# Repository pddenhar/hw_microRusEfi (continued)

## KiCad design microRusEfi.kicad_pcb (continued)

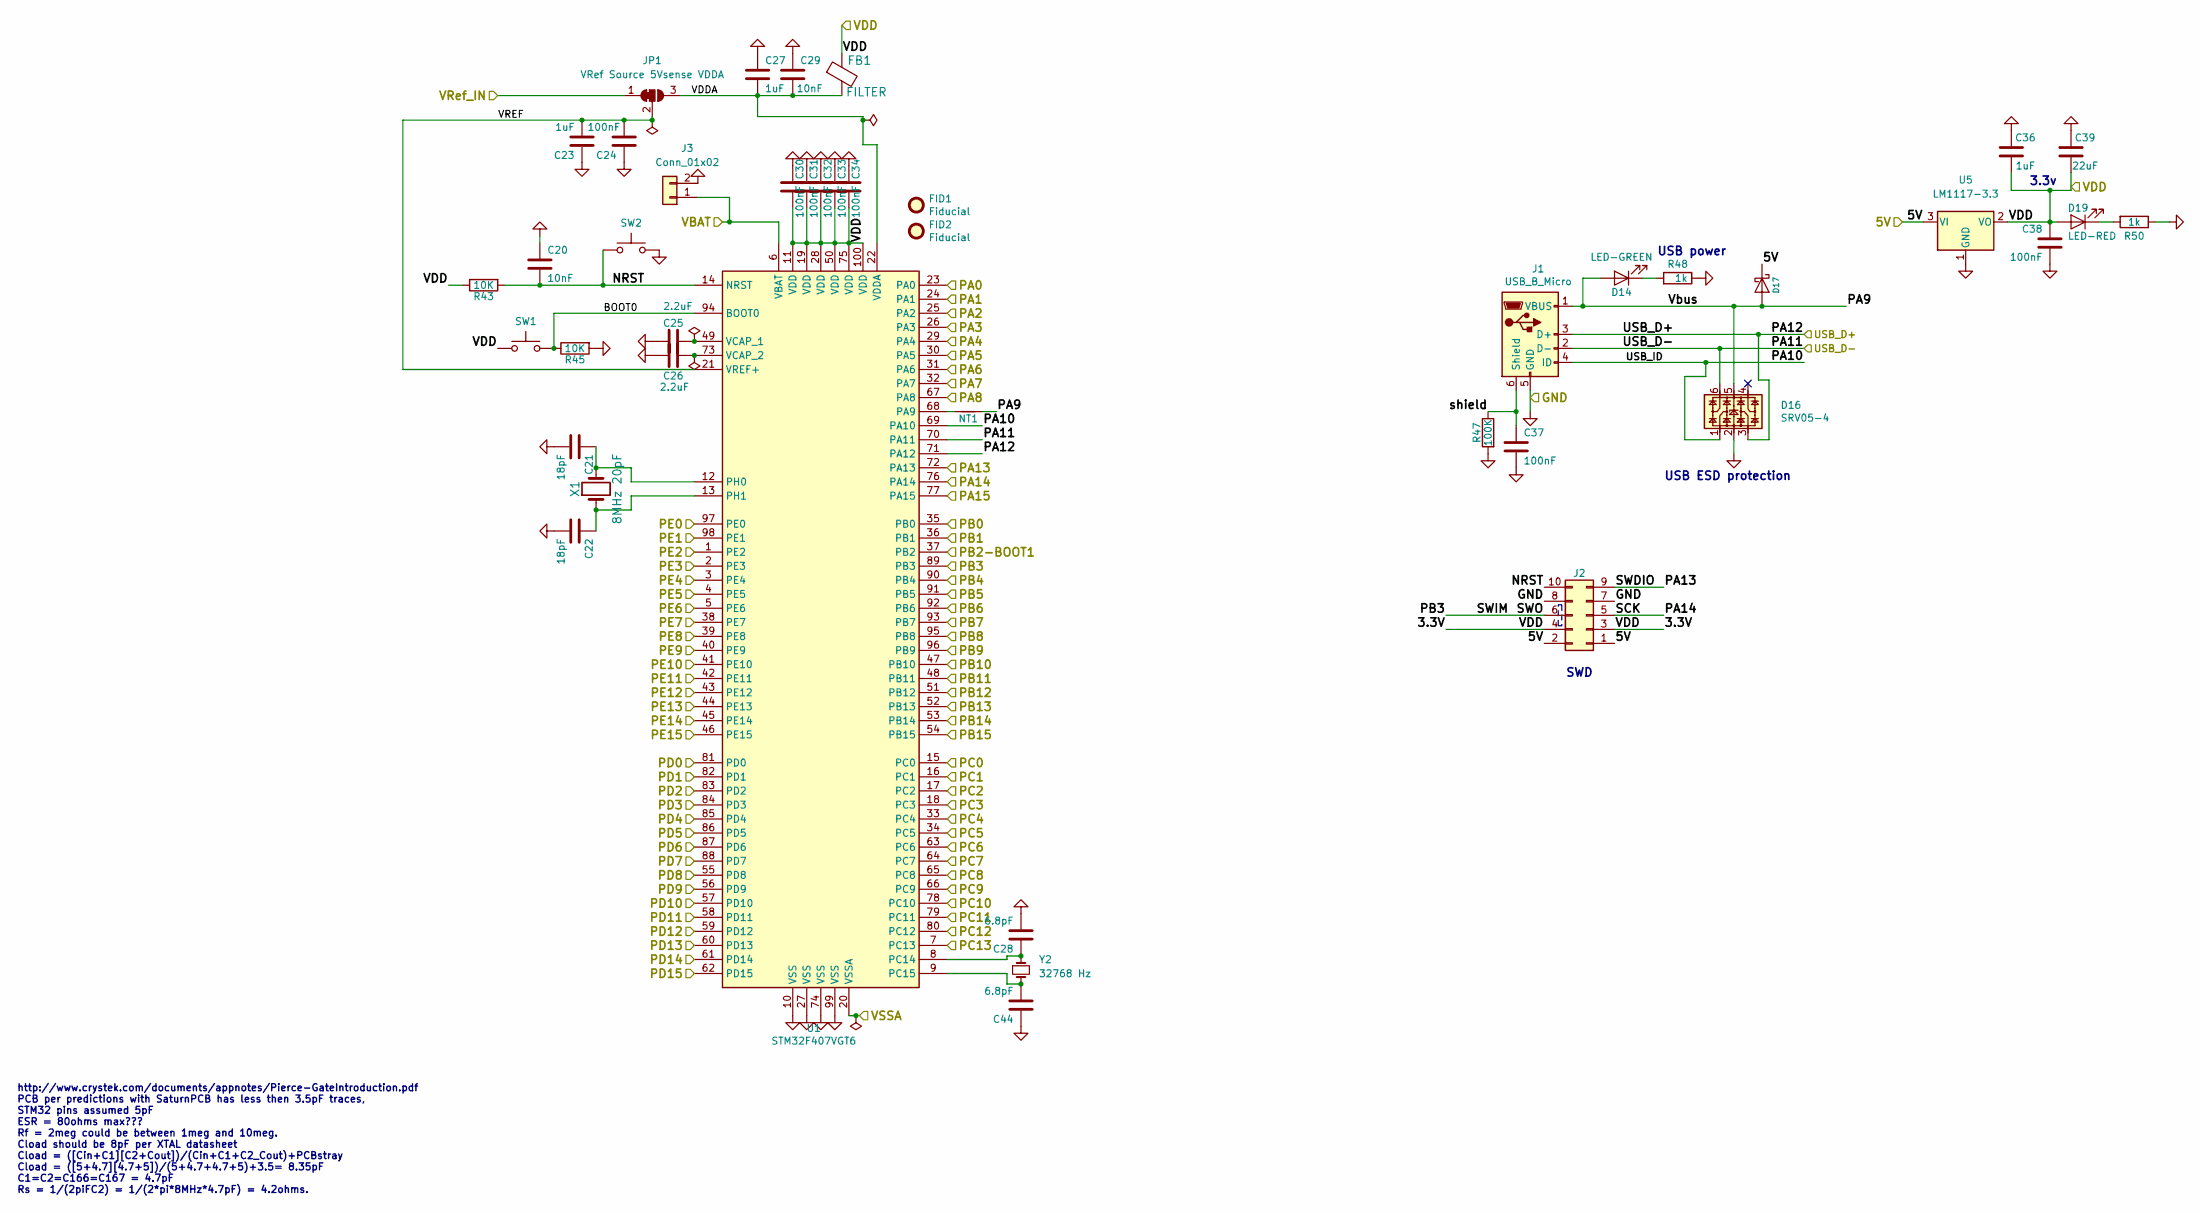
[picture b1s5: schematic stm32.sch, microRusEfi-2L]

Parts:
C20, C29: 10nF; C_0603_1608Metric; Part # C0603C103K1RACTU; LCSC C57112
C21, C22: 18pF; C_0603_1608Metric; Part # CC0603CRNPO9BN4R7; LCSC C1647
C23, C27, C36: 1uF; C_0603_1608Metric; Part # UMK107BJ105KA-T; LCSC C15849
C24, C30, C31, C32, C33, C34: 100nF; C_0603_1608Metric; LCSC C14663
C25, C26: 2.2uF; C_0603_1608Metric; Part # GRM188R6YA225KA12D; LCSC C23630
C28, C44: 6.8pF; C_0603_1608Metric; LCSC C1679
C37, C38: 100nF; C_0603_1608Metric; Part # C0603C104J5RACTU; LCSC C14663
C39: 22uF; C_0603_1608Metric; LCSC C59461
D14: LED-GREEN; C_0805_2012Metric; LCSC C2297
D16: SRV05-4; SOT-23-6; Part # SRV05-4; LCSC C85364
D17: B5819W; D_SOD-123; LCSC C8598
D19: LED-RED; LED_0603_1608Metric; LCSC C2286
FB1: FILTER; R_0603_1608Metric_Pad1.05x0.95mm_HandSolder; Part # BLM21PG221SN1D; LCSC C1034
FID1, FID2: Fiducial; Fiducial_0.5mm_Mask1mm; Part # DNP
J1: USB_B_Micro; USB_Micro-B_Wuerth-614105150721_Vertical; Part # USB3131-30-0230-A
J2: Conn_02x05_Odd_Even; PinSocket_2x05_P2.54mm_Vertical_SMD; Part # 95278-801B10LF
J3: Conn_01x02; Molex_PicoBlade_53047-0210_1x02_P1.25mm_Vertical
JP1: VRef Source 5Vsense VDDA; SolderJumper-3_P1.3mm_Bridged12_Pad1.0x1.5mm
NT1: Net-Tie_2; Net-Tie_2_8.5mil
R43, R45: 10K; R_0603_1608Metric; Part # RMCF0603JT10K0; LCSC C25804
R47: 100K; R_0603_1608Metric; Part # RMCF0603JT100K; LCSC C25803
R48: 1k; R_0603_1608Metric; Part # RMCF0603JJ1K00; LCSC C21190
R50: 1k; R_0603_1608Metric; LCSC C21190
SW1: SW_Push; SW_Push_SPST_NO_Alps_SKRK; Part # TBD
SW2: SW_Push; SW_Push_SPST_NO_Alps_SKRK
U1: STM32F407VGT6; LQFP-100_14x14mm_P0.5mm; Part # STM32F407VGT6; LCSC C12345
U5: LM1117-3.3; SOT-223-3_TabPin2; LCSC C6186
X1: 8MHz 20pF; Crystal_SMD_5032-2Pin_5.0x3.2mm; LCSC C115962
Y2: 32768 Hz; Crystal_SMD_3215-2Pin_3.2x1.5mm; LCSC C32346

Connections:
/5V: D17.1 (K), J2.1, J2.2, U5.3 (VI); also elsewhere on the board
/ADC/AGND: U1.20 (VSSA); also elsewhere on the board
/AT1_MCU: U1.23 (PA0); also elsewhere on the board
/AT2_MCU: U1.24 (PA1); also elsewhere on the board
/AT3_MCU: U1.25 (PA2); also elsewhere on the board
/AT4_MCU: U1.26 (PA3); also elsewhere on the board
/AV1_MCU: U1.15 (PC0); also elsewhere on the board
/AV2_MCU: U1.31 (PA6); also elsewhere on the board
/AV3_MCU: U1.32 (PA7); also elsewhere on the board
/AV4_MCU: U1.17 (PC2); also elsewhere on the board
/AV5_MCU: U1.18 (PC3); also elsewhere on the board
/AV6_MCU: U1.33 (PC4); also elsewhere on the board
/AV7_MCU: U1.34 (PC5); also elsewhere on the board
/AV8_MCU: U1.35 (PB0); also elsewhere on the board
/AV9_MCU: U1.36 (PB1); also elsewhere on the board
/AV10_MCU: U1.29 (PA4); also elsewhere on the board
/CAM_MCU: U1.30 (PA5); also elsewhere on the board
/CRANK: U1.63 (PC6); also elsewhere on the board
/CS_TLE: U1.86 (PD5); also elsewhere on the board
/FlashMemory/CS: U1.46 (PE15); also elsewhere on the board
/FlashMemory/HOLD: U1.48 (PB11); also elsewhere on the board
/H-BRIDGE/DIR: U1.67 (PA8); also elsewhere on the board
/H-BRIDGE/DIS: U1.65 (PC8); also elsewhere on the board
/MCU/BOOT0: R45.1, SW1.2, U1.94 (BOOT0)
/MCU/NRST: C20.2, J2.10, R43.2, SW2.1, U1.14 (NRST)
/MCU/PA9: D14.2 (A), D16.5, D17.2 (A), J1.1 (VBUS), NT1.2
/MCU/PA10: D16.1, J1.4 (ID), U1.69 (PA10)
/MCU/PA13: J2.9, U1.72 (PA13)
/MCU/PA14: J2.5, U1.76 (PA14)
/MCU/PB2-BOOT1: U1.37 (PB2); also elsewhere on the board
/MCU/PB7: U1.93 (PB7)
/MCU/PB9: U1.96 (PB9)
/MCU/PB10: U1.47 (PB10); also elsewhere on the board
/MCU/PB13: U1.52 (PB13); also elsewhere on the board
/MCU/PB14: U1.53 (PB14); also elsewhere on the board
/MCU/PB15: U1.54 (PB15); also elsewhere on the board
/MCU/PC7: U1.64 (PC7); also elsewhere on the board
/MCU/PC9: U1.66 (PC9); also elsewhere on the board
/MCU/PC13: U1.7 (PC13)
/MCU/PD10: U1.57 (PD10)
/MCU/PD11: U1.58 (PD11)
/MCU/PD12: U1.59 (PD12)
/MCU/PD13: U1.60 (PD13)
/MCU/PD14: U1.61 (PD14)
/MCU/PD15: U1.62 (PD15)
/MCU/PE0: U1.97 (PE0)
/MCU/PE5: U1.4 (PE5)
/MCU/PE6: U1.5 (PE6)
/MCU/VBAT: J3.1, U1.6 (VBAT); also elsewhere on the board
/MCU/VDDA: C27.2, C29.2, FB1.2, JP1.3 (B), U1.22 (VDDA)
/MCU/VREF: C23.2, C24.2, JP1.2 (C), U1.21 (VREF+)
/MCU/shield: C37.1, J1.6 (Shield), R47.1
/PA15: U1.77 (PA15); also elsewhere on the board
/PB8: U1.95 (PB8); also elsewhere on the board
/PC10: U1.78 (PC10); also elsewhere on the board
/PC11: U1.79 (PC11); also elsewhere on the board
/PC12: U1.80 (PC12); also elsewhere on the board
/PD0: U1.81 (PD0); also elsewhere on the board
/PE1: U1.98 (PE1); also elsewhere on the board
/PE2: U1.1 (PE2); also elsewhere on the board
/PE3: U1.2 (PE3); also elsewhere on the board
/PE4: U1.3 (PE4); also elsewhere on the board
/SCK: J2.6, U1.89 (PB3); also elsewhere on the board
/SI: U1.91 (PB5); also elsewhere on the board
/SO: U1.90 (PB4); also elsewhere on the board
/TLE8888-1QK/CAN_RX: U1.51 (PB12); also elsewhere on the board
/TLE8888-1QK/CAN_TX: U1.92 (PB6); also elsewhere on the board
/TLE8888-1QK/INJ_IN_1: U1.45 (PE14); also elsewhere on the board
/TLE8888-1QK/INJ_IN_2: U1.44 (PE13); also elsewhere on the board
/TLE8888-1QK/INJ_IN_3: U1.43 (PE12); also elsewhere on the board
/TLE8888-1QK/INJ_IN_4: U1.42 (PE11); also elsewhere on the board
/TLE8888-1QK/IN_9: U1.41 (PE10); also elsewhere on the board
/TLE8888-1QK/IN_10: U1.40 (PE9); also elsewhere on the board
/TLE8888-1QK/IN_11: U1.39 (PE8); also elsewhere on the board
/TLE8888-1QK/IN_12: U1.38 (PE7); also elsewhere on the board
/TLE8888-1QK/LIN_RX: U1.56 (PD9); also elsewhere on the board
/TLE8888-1QK/LIN_TX: U1.55 (PD8); also elsewhere on the board
/USB_D+: D16.3, J1.3 (D+), U1.71 (PA12); also elsewhere on the board
/USB_D-: D16.6, J1.2 (D-), U1.70 (PA11); also elsewhere on the board
/VDD: C30.2, C31.2, C32.2, C33.2, C34.2, C36.2, C38.1, C39.2, D19.2 (A), FB1.1, J2.3, J2.4, R43.1, SW1.1, U1.11 (VDD), U1.19 (VDD), U1.28 (VDD), U1.50 (VDD), U1.75 (VDD), U1.100 (VDD), U5.2 (VO); also elsewhere on the board
/VSense_ref: JP1.1 (A); also elsewhere on the board
/Vbat_MCU: U1.16 (PC1); also elsewhere on the board
/hi-lo/GP5_MCU: U1.88 (PD7); also elsewhere on the board
/hi-lo/GP6_MCU: U1.87 (PD6); also elsewhere on the board
/hi-lo/Ign1_MCU: U1.85 (PD4); also elsewhere on the board
/hi-lo/Ign2_MCU: U1.84 (PD3); also elsewhere on the board
/hi-lo/Ign3_MCU: U1.83 (PD2); also elsewhere on the board
/hi-lo/Ign4_MCU: U1.82 (PD1); also elsewhere on the board
GND: C20.1, C21.2, C22.2, C23.1, C24.1, C25.2, C26.2, C27.1, C28.2, C29.1, C30.1, C31.1, C32.1, C33.1, C34.1, C36.1, C37.2, C38.2, C39.1, C44.1, D16.2, J1.5 (GND), J2.7, J2.8, J3.2, R45.2, R47.2, R48.1, R50.1, SW2.2, U1.10 (VSS), U1.27 (VSS), U1.74 (VSS), U1.99 (VSS), U5.1 (GND); also elsewhere on the board
unnamed: C21.1, U1.12 (PH0), X1.2
unnamed: C22.1, U1.13 (PH1), X1.1
unnamed: C25.1, U1.49 (VCAP_1)
unnamed: C26.1, U1.73 (VCAP_2)
unnamed: C28.1, U1.8 (PC14), Y2.1
unnamed: C44.2, U1.9 (PC15), Y2.2
unnamed: D14.1 (K), R48.2
unnamed: D19.1 (K), R50.2
unnamed: NT1.1, U1.68 (PA9)

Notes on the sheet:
SWD
USB power
3.3v
USB ESD protection
http://www.crystek.com/documents/appnotes/Pierce-GateIntroduction.pdf PCB per predictions with SaturnPCB has less then 3.5pF traces, STM32 pins assumed 5pF ESR = 80ohms max??? Rf = 2meg could be between 1meg and 10meg. Cload should be 8pF per XTAL datasheet Cload = ([Cin+C1][C2+Cout])/(Cin+C1+C2_Co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

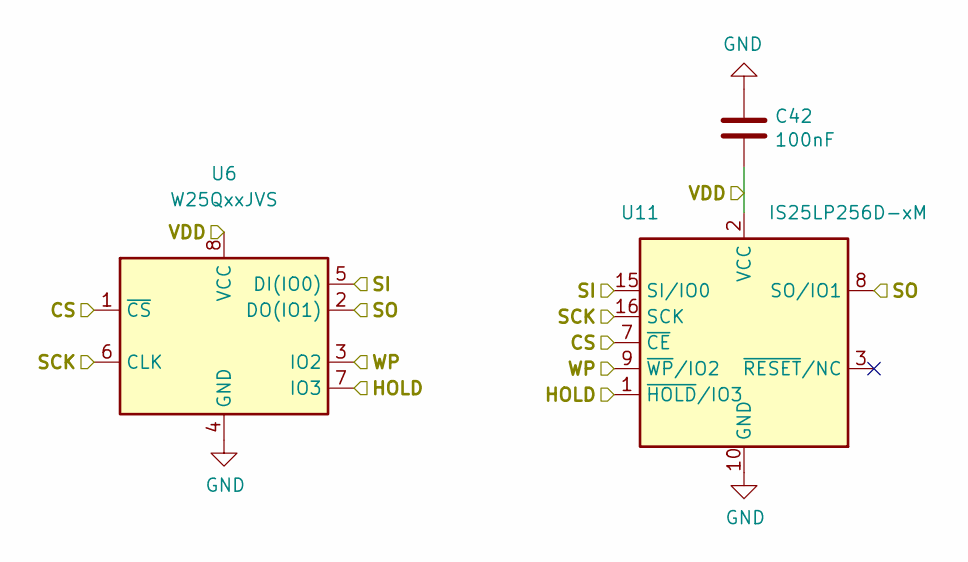
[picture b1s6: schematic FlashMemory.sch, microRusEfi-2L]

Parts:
C42: 100nF; C_0603_1608Metric; Part # C0603C104J5RACTU; LCSC C14663
U6: W25QxxJVS; SO-8_5.3x6.2mm_P1.27mm-150+208; LCSC C97521
U11: IS25LP256D-xM; SOIC-16W_7.5x10.3mm_P1.27mm; Part # IS25LP256D-RMLE

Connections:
/FlashMemory/CS: U6.1 (~CS), U11.7 (~CE); also elsewhere on the board
/FlashMemory/HOLD: U6.7 (IO3), U11.1 (~HOLD~/IO3); also elsewhere on the board
/MCU/PB10: U6.3 (IO2), U11.9 (~WP~/IO2); also elsewhere on the board
/MCU/PB13: U6.6 (CLK), U11.16 (SCK); also elsewhere on the board
/MCU/PB14: U6.2 (DO(IO1)), U11.8 (SO/IO1); also elsewhere on the board
/MCU/PB15: U6.5 (DI(IO0)), U11.15 (SI/IO0); also elsewhere on the board
/VDD: C42.2, U6.8 (VCC), U11.2 (VCC); also elsewhere on the board
GND: C42.1, U6.4 (GND), U11.10 (GND); also elsewhere on the board

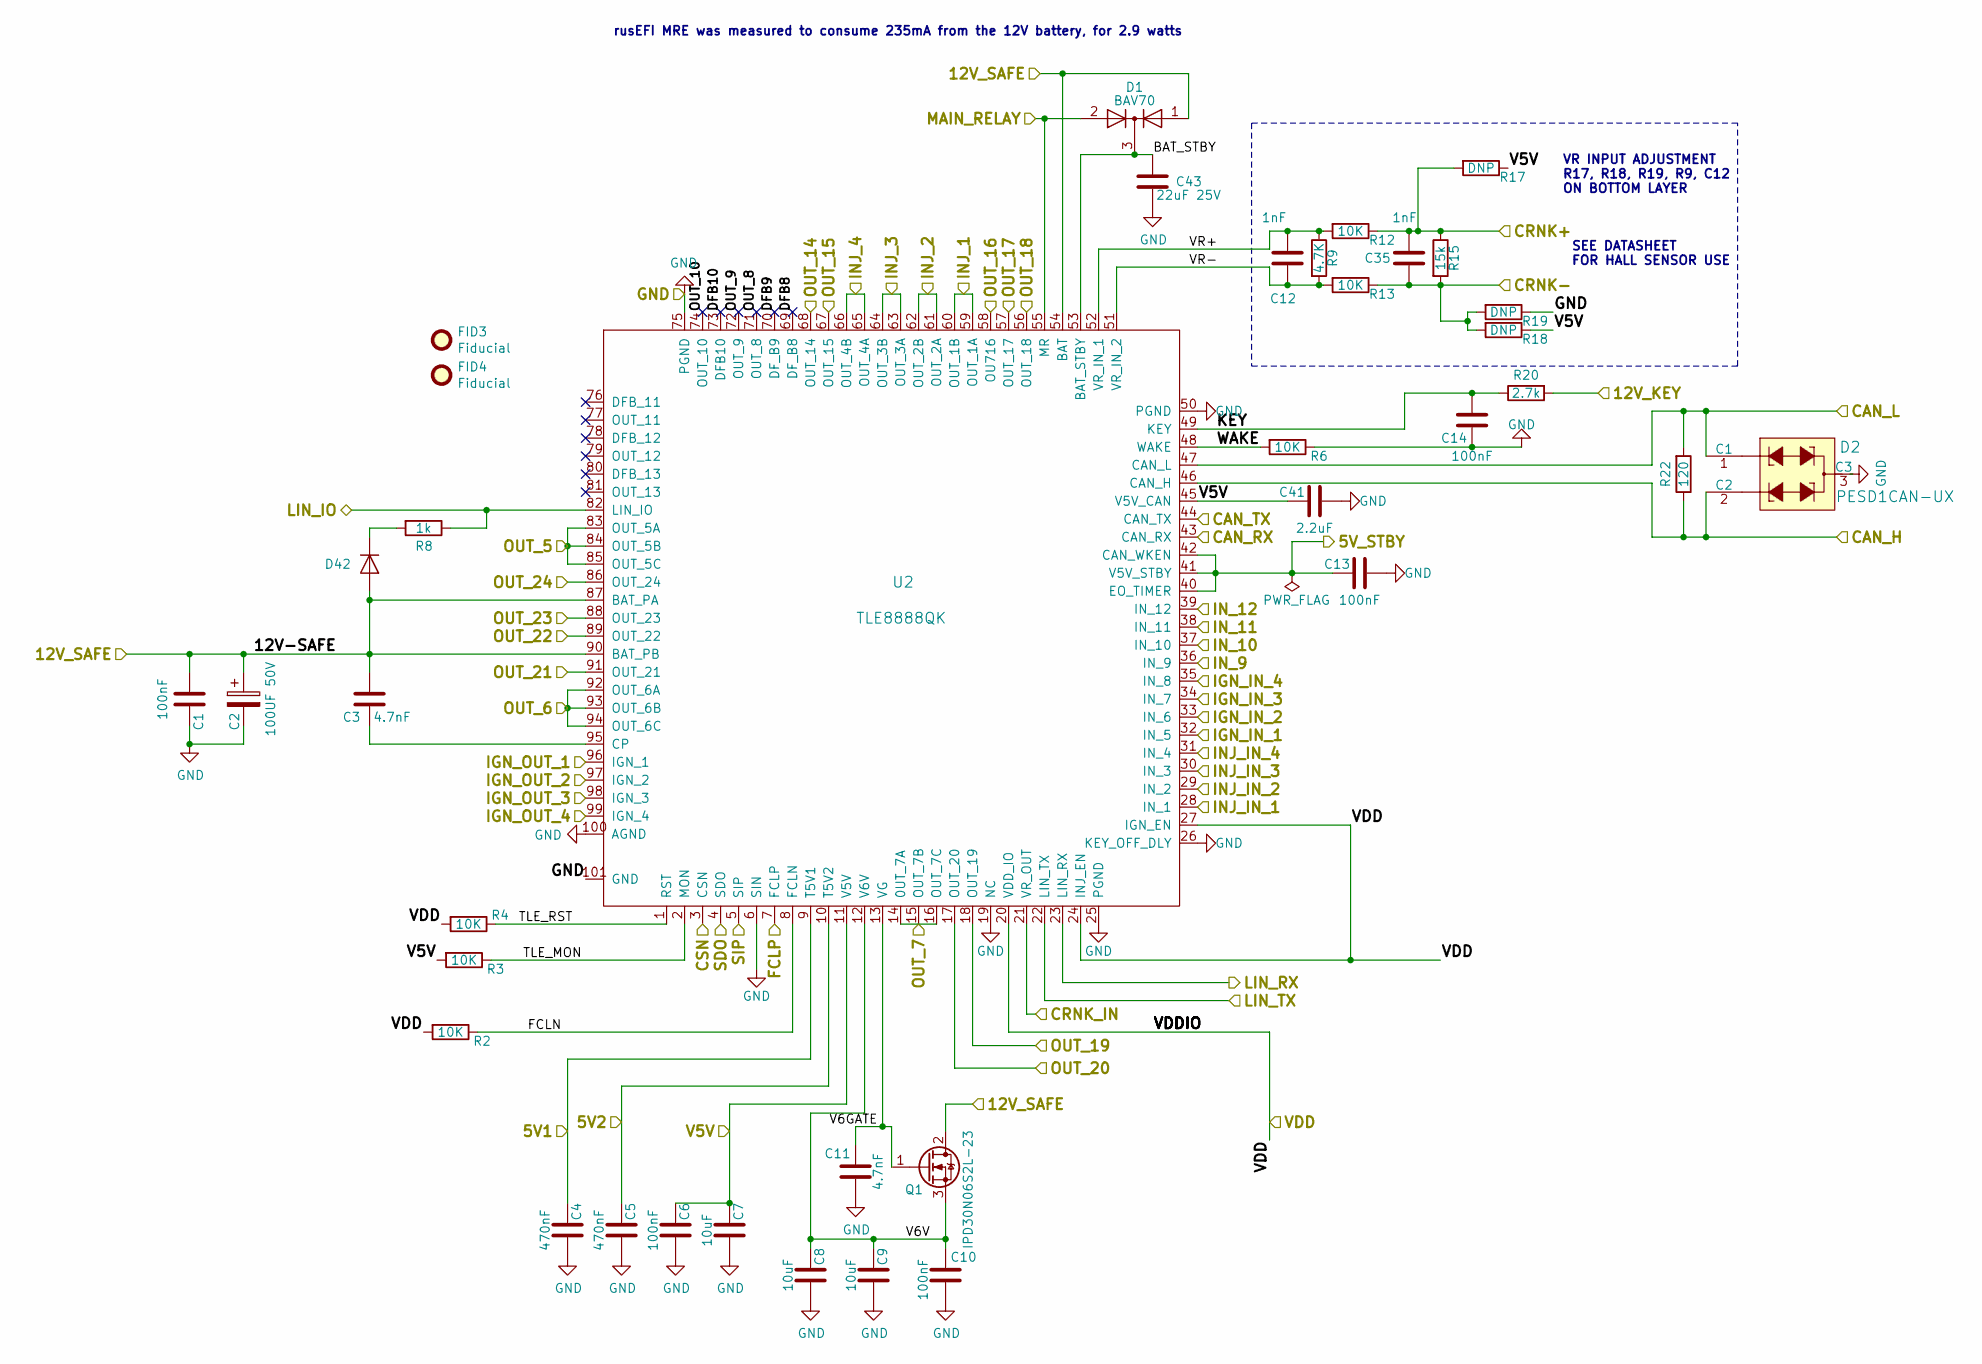
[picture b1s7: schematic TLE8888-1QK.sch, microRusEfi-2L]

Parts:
C1, C6, C10, C13, C14: 100nF; C_0603_1608Metric; Part # C0603C104J5RACTU; LCSC C14663
C2: 100UF 50V; CP_Elec_8x10.5; Part # UCD1H101MNL1GS
C3, C11: 4.7nF; C_0603_1608Metric; Part # CGA3E2X7R1H472K080AA; LCSC C53987
C4, C5: 470nF; C_0603_1608Metric; Part # CGA3E3X7R1H474K080AE; LCSC C1623
C7, C8, C9: 10uF; C_0603_1608Metric; Part # C1608X5R1E106M080AC; LCSC C19702
C12, C35: 1nF; C_0603_1608Metric; Part # GRM1885C1H102FA01D; LCSC C1588
C41: 2.2uF; C_0603_1608Metric; LCSC C23630
C43: 22uF 25V; C_0805_2012Metric; Part # C1608X5R1E106M080AC; LCSC C45783
D1: BAV70; SOT-23; LCSC C68978
D2: PESD1CAN-UX; SOT-23; Part # PESD1CANUX
D42: 1N4148WS; D_SOD-323; Part # NSR0530HT; LCSC C2128
FID3, FID4: Fiducial; Fiducial_0.5mm_Mask1mm; Part # DNP
Q1: IPD30N06S2L-23; TO-252-2; Part # IPD30N06S2L23AT3
R2, R3, R4, R6: 10K; R_0603_1608Metric; LCSC C25804
R8: 1k; R_0603_1608Metric; Part # RMCF0603JJ1K00; LCSC C21190
R9: 4.7K; R_0603_1608Metric; LCSC C23162
R12, R13: 10K; R_0603_1608Metric; Part # RMCF0603JT10K0; LCSC C25804
R15: 15k; R_0603_1608Metric; Part # RMCF0603JG15K0; LCSC C22809
R17, R18, R19: DNP; R_0603_1608Metric; Part # DNP
R20: 2.7k; R_0603_1608Metric; Part # RMCF0603FT2K70; LCSC C13167
R22: 120; R_0805_2012Metric; LCSC C17437
U2: TLE8888QK; LQFP-100_14x14mm_P0.5mm_THERMAL; Part # TLE88882QKXUMA1

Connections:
/5V: C6.1, C7.1, C41.1, R3.2, R17.1, R18.1, U2.11 (V5V), U2.45 (V5V_CAN); also elsewhere on the board
/5V1: C5.1, U2.10 (T5V2); also elsewhere on the board
/5V2: C4.1, U2.9 (T5V1); also elsewhere on the board
/12V_KEY: R20.2; also elsewhere on the board
/12V_SAFE: C1.1, C2.1, C3.1, D1.1 (A), D42.2 (A), Q1.2 (D), U2.54 (BAT), U2.87 (BAT_PA), U2.90 (BAT_PB); also elsewhere on the board
/CANH: D2.2 (C2), R22.1, U2.46 (CAN_H); also elsewhere on the board
/CANL: D2.1 (C1), R22.2, U2.47 (CAN_L); also elsewhere on the board
/CRANK: U2.21 (VR_OUT); also elsewhere on the board
/CRNK+: C35.1, R12.1, R15.1, R17.2; also elsewhere on the board
/CRNK-: C35.2, R13.1, R15.2, R18.2, R19.2; also elsewhere on the board
/CS_TLE: U2.3 (CSN); also elsewhere on the board
/GP1: U2.91 (OUT_21); also elsewhere on the board
/GP2: U2.89 (OUT_22); also elsewhere on the board
/GP3: U2.88 (OUT_23); also elsewhere on the board
/GP4: U2.86 (OUT_24); also elsewhere on the board
/INJECTOR-1: U2.59 (OUT_1A), U2.60 (OUT_1B); also elsewhere on the board
/INJECTOR-2: U2.61 (OUT_2A), U2.62 (OUT_2B); also elsewhere on the board
/INJECTOR-3: U2.63 (OUT_3A), U2.64 (OUT_3B); also elsewhere on the board
/INJECTOR-4: U2.65 (OUT_4A), U2.66 (OUT_4B); also elsewhere on the board
/LINBUS: R8.1, U2.82 (LIN_IO); also elsewhere on the board
/LS1: U2.92 (OUT_6A), U2.93 (OUT_6B), U2.94 (OUT_6C); also elsewhere on the board
/LS2: U2.83 (OUT_5A), U2.84 (OUT_5B), U2.85 (OUT_5C); also elsewhere on the board
/MAIN_RELAY: D1.2 (A), U2.55 (MR); also elsewhere on the board
/SCK: U2.7 (FCLP); also elsewhere on the board
/SI: U2.5 (SIP); also elsewhere on the board
/SO: U2.4 (SDO); also elsewhere on the board
/TLE8888-1QK/5V_STBY: C13.1, U2.40 (EO_TIMER), U2.41 (V5V_STBY), U2.42 (CAN_WKEN); also elsewhere on the board
/TLE8888-1QK/BAT_STBY: C43.1, D1.3 (K), U2.53 (BAT_STBY)
/TLE8888-1QK/CAN_RX: U2.43 (CAN_RX); also elsewhere on the board
/TLE8888-1QK/CAN_TX: U2.44 (CAN_TX); also elsewhere on the board
/TLE8888-1QK/DFB8: U2.69 (DF_B8)
/TLE8888-1QK/DFB9: U2.70 (DF_B9)
/TLE8888-1QK/DFB10: U2.73 (DFB10)
/TLE8888-1QK/FCLN: R2.1, U2.8 (FCLN)
/TLE8888-1QK/IGN_OUT_1: U2.96 (IGN_1); also elsewhere on the board
/TLE8888-1QK/IGN_OUT_2: U2.97 (IGN_2); also elsewhere on the board
/TLE8888-1QK/IGN_OUT_3: U2.98 (IGN_3); also elsewhere on the board
/TLE8888-1QK/IGN_OUT_4: U2.99 (IGN_4); also elsewhere on the board
/TLE8888-1QK/INJ_IN_1: U2.28 (IN_1); also elsewhere on the board
/TLE8888-1QK/INJ_IN_2: U2.29 (IN_2); also elsewhere on the board
/TLE8888-1QK/INJ_IN_3: U2.30 (IN_3); also elsewhere on the board
/TLE8888-1QK/INJ_IN_4: U2.31 (IN_4); also elsewhere on the board
/TLE8888-1QK/IN_9: U2.36 (IN_9); also elsewhere on the board
/TLE8888-1QK/IN_10: U2.37 (IN_10); also elsewhere on the board
/TLE8888-1QK/IN_11: U2.38 (IN_11); also elsewhere on the board
/TLE8888-1QK/IN_12: U2.39 (IN_12); also elsewhere on the board
/TLE8888-1QK/KEY: C14.1, R20.1, U2.49 (KEY)
/TLE8888-1QK/LIN_RX: U2.23 (LIN_RX); also elsewhere on the board
/TLE8888-1QK/LIN_TX: U2.22 (LIN_TX); also elsewhere on the board
/TLE8888-1QK/OUT_7: U2.14 (0UT_7A), U2.15 (OUT_7B), U2.16 (OUT_7C)
/TLE8888-1QK/OUT_8: U2.71 (OUT_8)
/TLE8888-1QK/OUT_9: U2.72 (OUT_9)
/TLE8888-1QK/OUT_10: U2.74 (OUT_10)
/TLE8888-1QK/OUT_14: U2.68 (OUT_14); also elsewhere on the board
/TLE8888-1QK/OUT_15: U2.67 (OUT_15); also elsewhere on the board
/TLE8888-1QK/OUT_16: U2.58 (OU716); also elsewhere on the board
/TLE8888-1QK/OUT_17: U2.57 (OUT_17); also elsewhere on the board
/TLE8888-1QK/OUT_18: U2.56 (OUT_18); also elsewhere on the board
/TLE8888-1QK/OUT_19: U2.18 (OUT_19)
/TLE8888-1QK/OUT_20: U2.17 (OUT_20)
/TLE8888-1QK/TLE_MON: R3.1, U2.2 (MON)
/TLE8888-1QK/TLE_RST: R4.1, U2.1 (RST)
/TLE8888-1QK/V6GATE: C11.1, Q1.1 (G), U2.13 (VG)
/TLE8888-1QK/V6V: C8.1, C9.1, C10.1, Q1.3 (S), U2.12 (V6V)
/TLE8888-1QK/VR+: C12.1, R9.1, R12.2, U2.52 (VR_IN_1)
/TLE8888-1QK/VR-: C12.2, R9.2, R13.2, U2.51 (VR_IN_2)
/TLE8888-1QK/WAKE: R6.2, U2.48 (WAKE)
/VDD: R2.2, R4.2, U2.20 (VDD_IO), U2.24 (INJ_EN), U2.27 (IGN_EN); also elsewhere on the board
GND: C1.2, C2.2, C4.2, C5.2, C6.2, C7.2, C8.2, C9.2, C10.2, C11.2, C13.2, C14.2, C41.2, C43.2, D2.3 (C3), R6.1, R19.1, U2.6 (SIN), U2.19 (NC), U2.25 (PGND), U2.26 (KEY_OFF_DLY), U2.32 (IN_5), U2.33 (IN_6), U2.34 (IN_7), U2.35 (IN_8), U2.50 (PGND), U2.75 (PGND), U2.100 (AGND), U2.101 (GND); also elsewhere on the board
unnamed: C3.2, U2.95 (CP)
unnamed: D42.1 (K), R8.2

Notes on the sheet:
VR INPUT ADJUSTMENT R17, R18, R19, R9, C12 ON BOTTOM LAYER
SEE DATASHEET FOR HALL SENSOR USE
rusEFI MRE was measured to consume 235mA from the 12V battery, for 2.9 watts

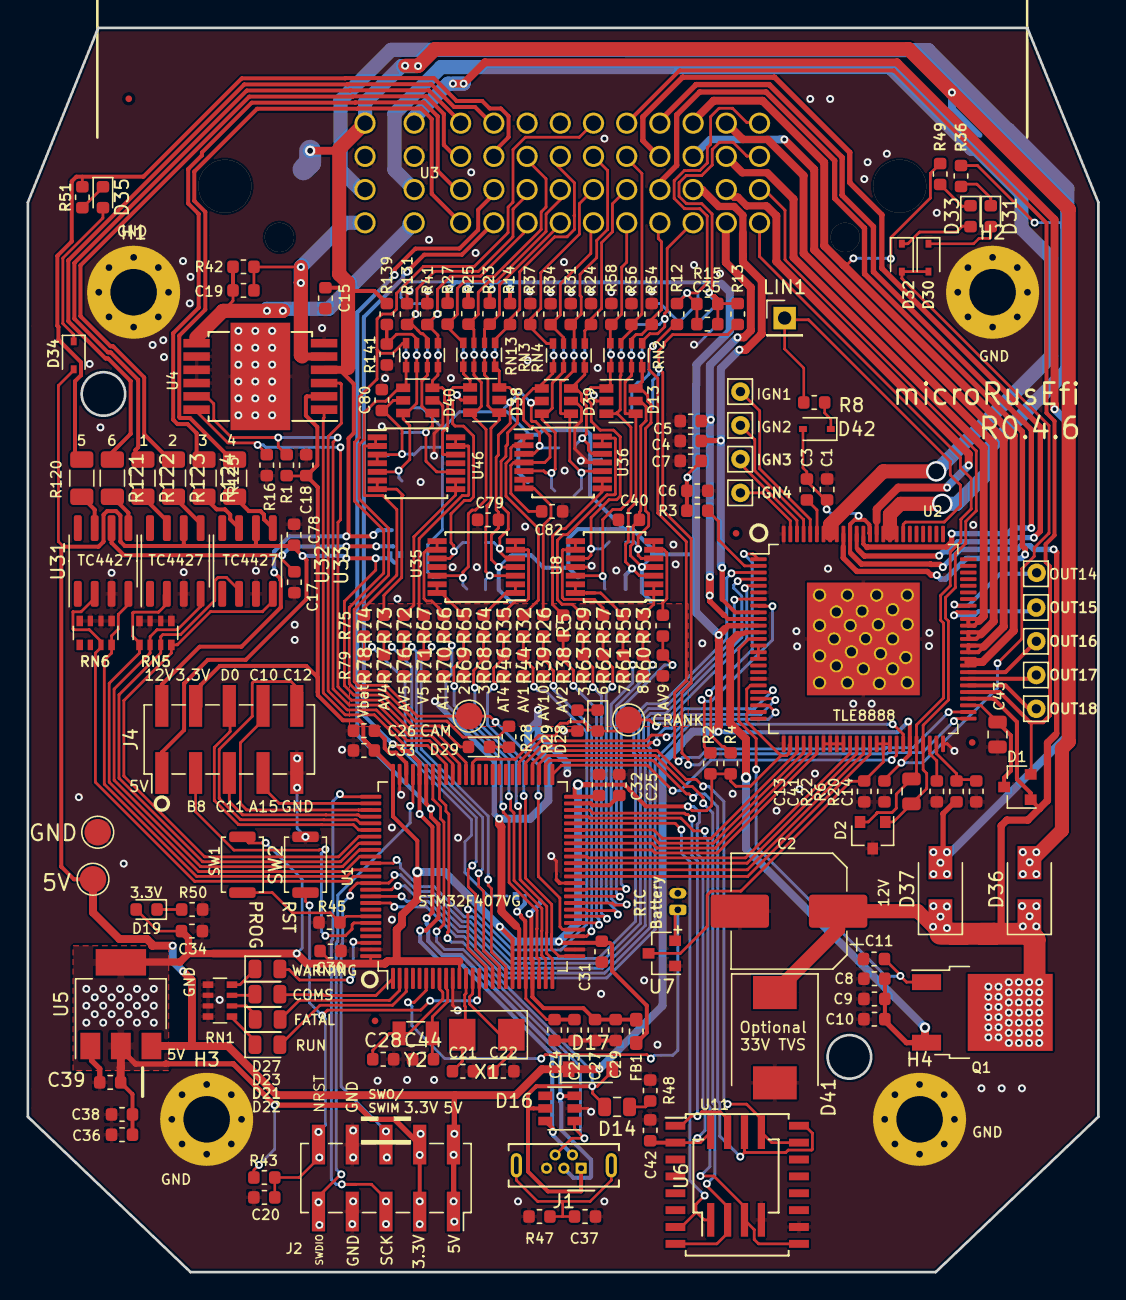
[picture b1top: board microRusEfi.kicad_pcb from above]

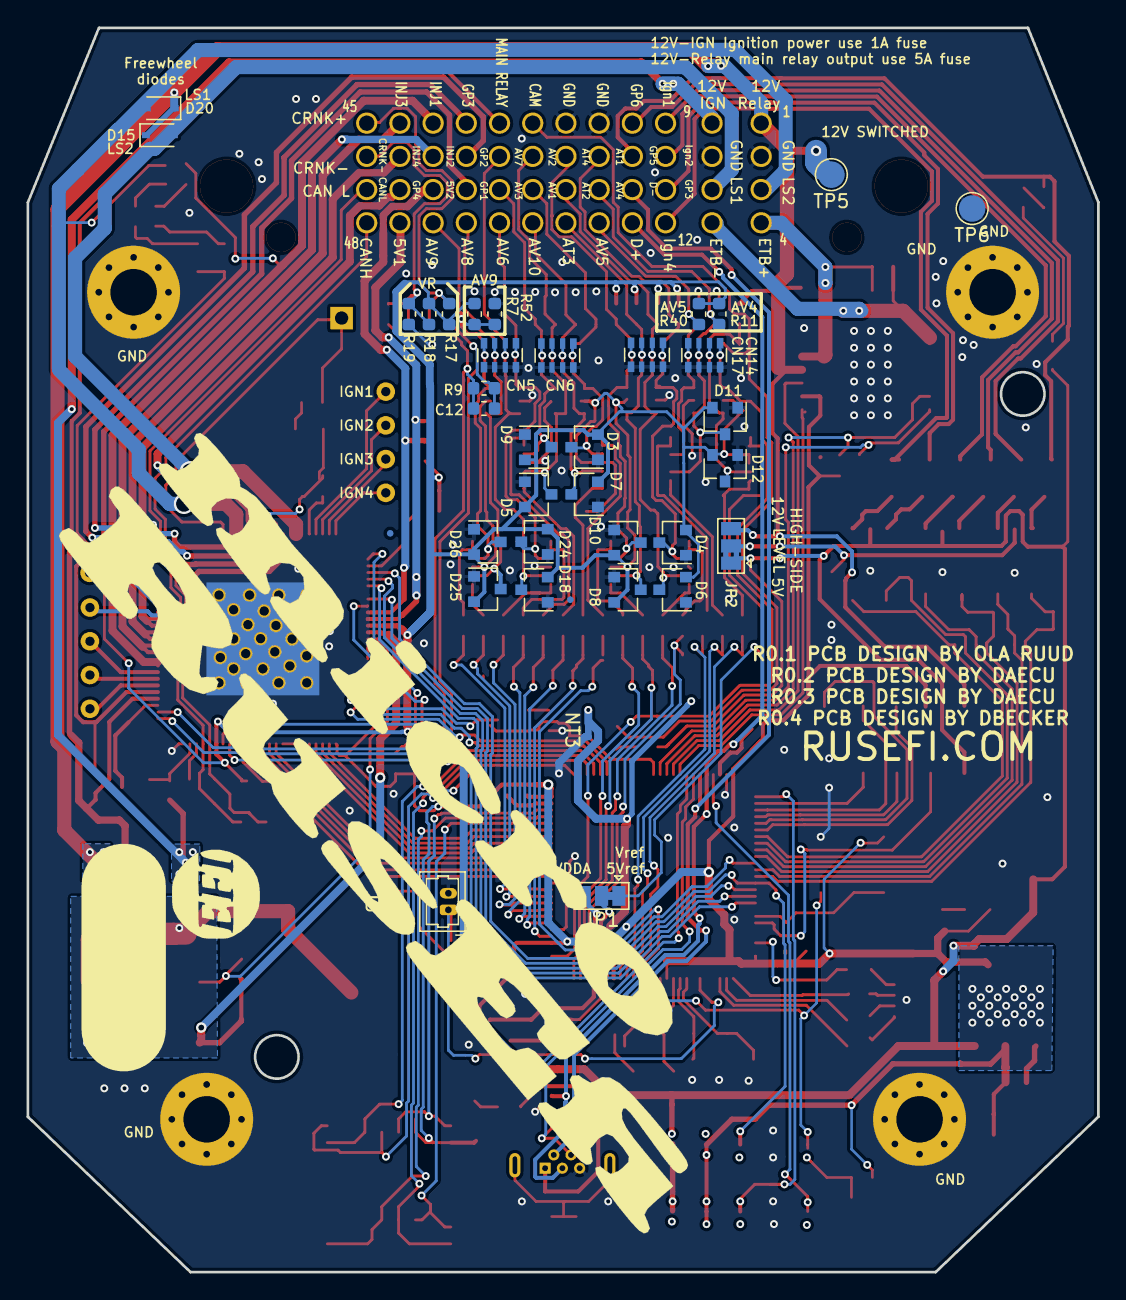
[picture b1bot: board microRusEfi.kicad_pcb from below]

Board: 2 copper layers, 80.6 x 93.7 mm, 242 parts (38 on the bottom side), 204 nets.

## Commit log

2019-10-25 Fix broken rescue symbol on schematic (LOGO)
2019-10-25 Replace micro USB connector with through hole version
2019-10-25 Use mounting hole components on PCB instead of vias with filled zones
2019-10-25 Rotate USB connector to follow wide-side-down orientation expectation.
2019-10-25 Remove thermal breaks from bottom layer TLE8888 pad
2019-10-25 Add diode and pull up on linbus. Fix some KiCAD 4.0 footprint problems
2019-10-26 Move reset and boot buttons to be next to each other
2019-10-26 Fix a few DRC errors probably introduced by me
2019-10-26 Clean up tracks and vias
2019-10-26 Missing GND connection on CRNK-
2019-11-08 Fix mixed up AV4, AV5, 5Vsense, and 12V sense
2019-11-08 Add 0.4.6 gerbers that were submitted to PCBWay
